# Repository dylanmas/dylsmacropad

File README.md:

# WIP!

Visit the wiki to learn more.

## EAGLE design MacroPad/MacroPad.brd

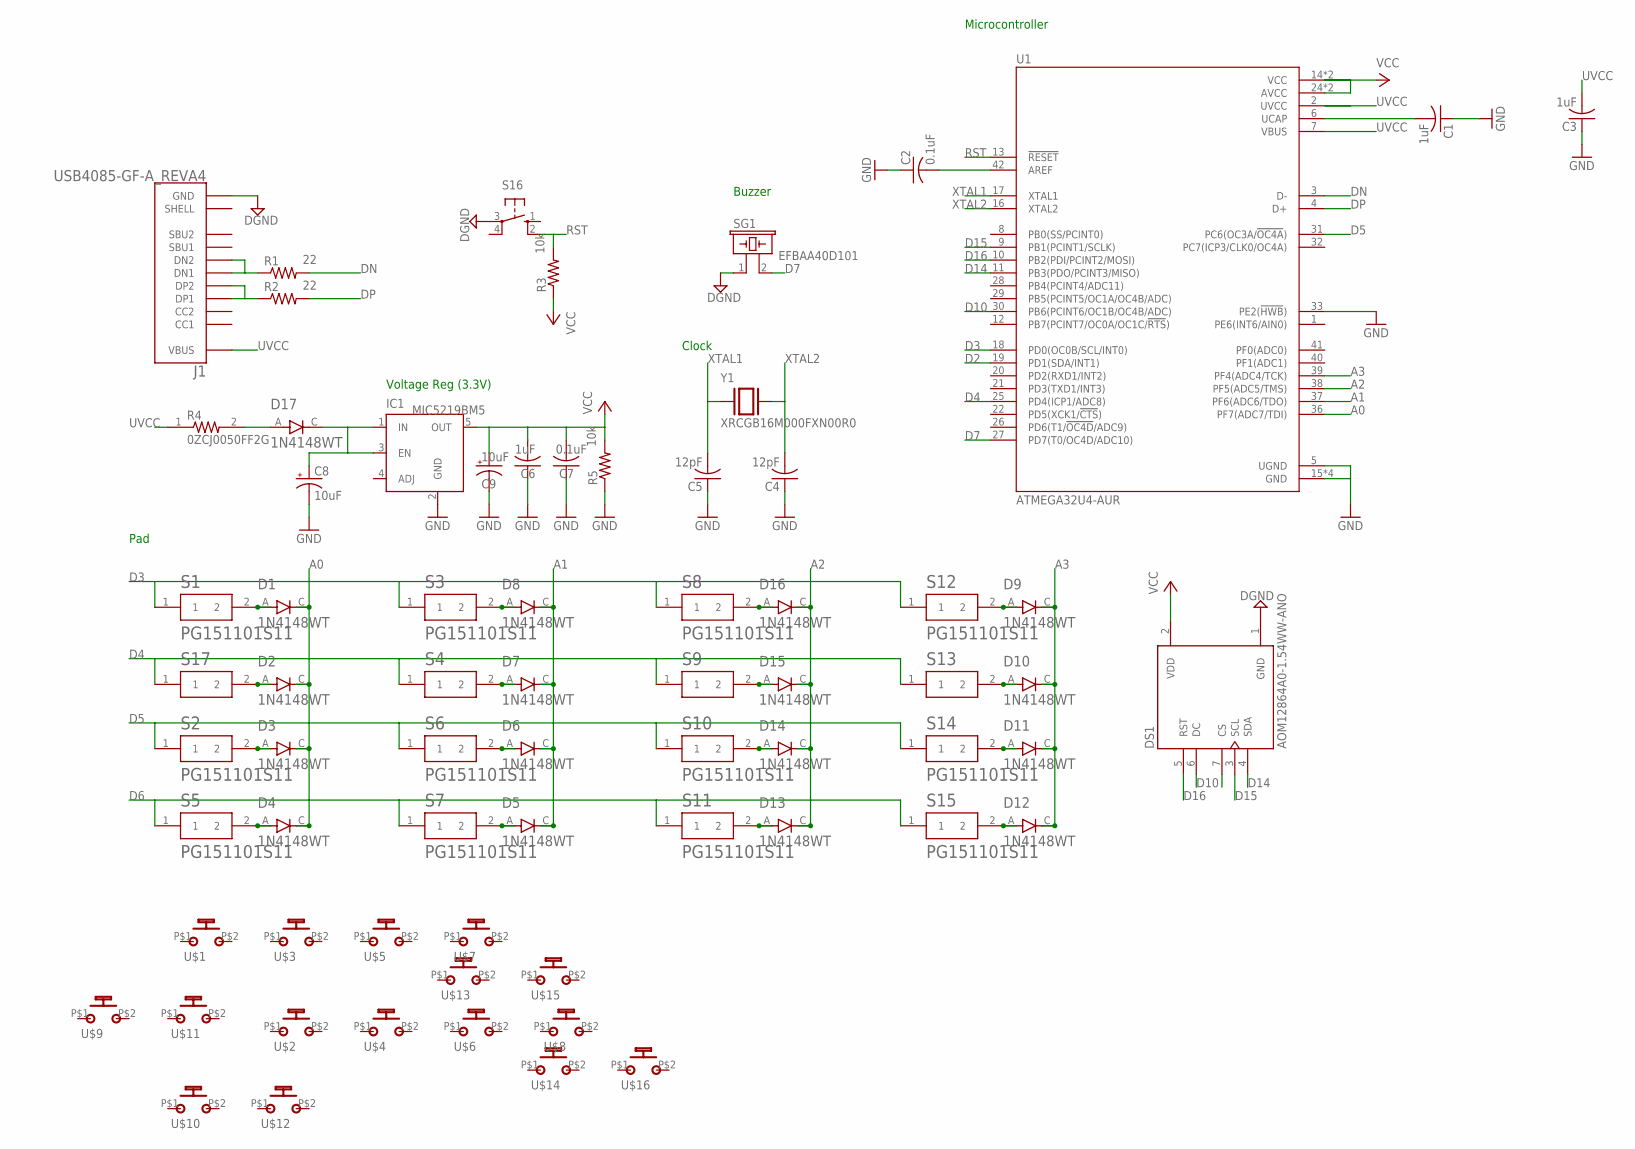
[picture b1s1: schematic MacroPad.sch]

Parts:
C1, C3, C6: 1uF; C0603
C2, C7: 0.1uF; C0603
C4, C5: 12pF; C0603
C8, C9: 10uF; 153CLV-0605
D1, D2, D3, D4, D5, D6, D7, D8, D9, D10, D11, D12, D13, D14, D15, D16, D17: 1N4148WT; SODFL1608X70N
DS1: AOM12864A0-1.54WW-ANO; LCD_AOM12864A0-1.54WW-ANO
IC1: MIC5219BM5; SOT23-5
J1: USB4085-GF-A_REVA4; GCT_USB4085-GF-A_REVA4
R1, R2: 22; R0805
R3, R5: 10k; R0805
R4: 0ZCJ0050FF2G; RESC3216X125N
S1, S2, S3, S4, S5, S6, S7, S8, S9, S10, S11, S12, S13, S14, S15, S17: PG151101S11; SW_PG151101S11
S16: 10-XX; B3F-10XX
SG1: EFBAA40D101
U1: ATMEGA32U4-AUR; QFP80P1200X1200X120-44N
U$1, U$2, U$3, U$4, U$5, U$6, U$7, U$8, U$9, U$10, U$11, U$12, U$13, U$14, U$15, U$16: MX1A-11NN; CHERRY_MX1A-11NN_SWITCH
Y1: XRCGB16M000FXN00R0; OSC_XRCGB16M000FXN00R0

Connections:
A0: D1.C, D2.C, D3.C, D4.C, U1.36 (PF7(ADC7/TDI))
A1: D5.C, D6.C, D7.C, D8.C, U1.37 (PF6(ADC6/TDO))
A2: D13.C, D14.C, D15.C, D16.C, U1.38 (PF5(ADC5/TMS))
A3: D9.C, D10.C, D11.C, D12.C, U1.39 (PF4(ADC4/TCK))
D2: U1.19 (PD1(SDA/INT1))
D3: S1.1, S3.1, S8.1, S12.1, U1.18 (PD0(OC0B/SCL/INT0))
D4: S4.1, S9.1, S13.1, S17.1, U1.25 (PD4(ICP1/ADC8))
D5: S2.1, S6.1, S10.1, S14.1, U1.31 (PC6(OC3A/!OC4A!))
D6: S5.1, S7.1, S11.1, S15.1
D7: SG1.2, U1.27 (PD7(T0/OC4D/ADC10))
D10: DS1.6 (DC), U1.30 (PB6(PCINT6/OC1B/OC4B/ADC))
D14: DS1.4 (SDA), U1.11 (PB3(PDO/PCINT3/MISO))
D15: DS1.3 (SCL), U1.9 (PB1(PCINT1/SCLK))
D16: DS1.5 (RST), U1.10 (PB2(PDI/PCINT2/MOSI))
DGND: DS1.1 (GND), J1.A1 (GND), J1.A12 (GND), J1.B1 (GND), J1.B12 (GND), S16.3, SG1.1
DN: R1.2, U1.3 (D-)
DP: R2.2, U1.4 (D+)
GND: C1.1, C2.1, C3.1, C4.1, C5.1, C6.1, C7.1, C8.-, C9.-, IC1.2 (GND), R5.1, U1.5 (UGND), U1.15 (GND), U1.23 (GND), U1.33 (PE2(!HWB!)), U1.35 (GND), U1.43 (GND)
unnamed: D1.A, S1.2
unnamed: D2.A, S17.2
unnamed: D3.A, S2.2
unnamed: D4.A, S5.2
unnamed: D8.A, S3.2
unnamed: D7.A, S4.2
unnamed: D6.A, S6.2
unnamed: D5.A, S7.2
unnamed: D16.A, S8.2
unnamed: D15.A, S9.2
unnamed: D14.A, S10.2
unnamed: D13.A, S11.2
unnamed: D9.A, S12.2
unnamed: D10.A, S13.2
unnamed: D11.A, S14.2
unnamed: D12.A, S15.2
unnamed: D17.A, R4.2
unnamed: J1.A7 (DN1), J1.B7 (DN2), R1.1
unnamed: J1.A6 (DP1), J1.B6 (DP2), R2.1
unnamed: C1.2, U1.6 (UCAP)
unnamed: C2.2, U1.42 (AREF)
unnamed: C8.+, D17.C, IC1.1 (IN), IC1.3 (EN)
RST: R3.2, S16.2 (S1), U1.13 (!RESET)
UVCC: C3.2, J1.A4 (VBUS), J1.A9 (VBUS), J1.B4 (VBUS), J1.B9 (VBUS), R4.1, U1.2 (UVCC), U1.7 (VBUS)
VCC: C6.2, C7.2, C9.+, DS1.2 (VDD), IC1.5 (OUT), R3.1, R5.2, U1.14 (VCC), U1.24 (AVCC), U1.34 (VCC), U1.44 (AVCC)
XTAL1: C5.2, U1.17 (XTAL1), Y1.1
XTAL2: C4.2, U1.16 (XTAL2), Y1.3

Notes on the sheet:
Pad
Buzzer
Microcontroller
Clock
Voltage Reg (3.3V)

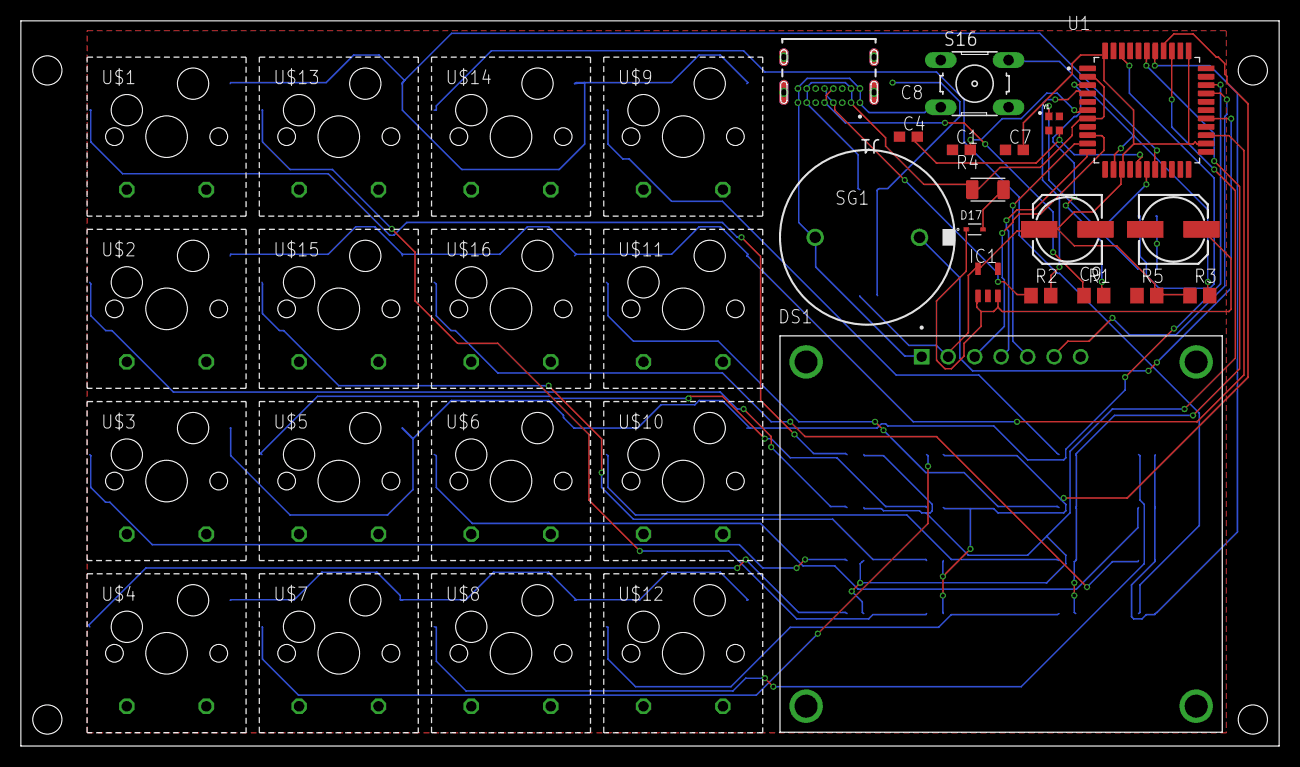
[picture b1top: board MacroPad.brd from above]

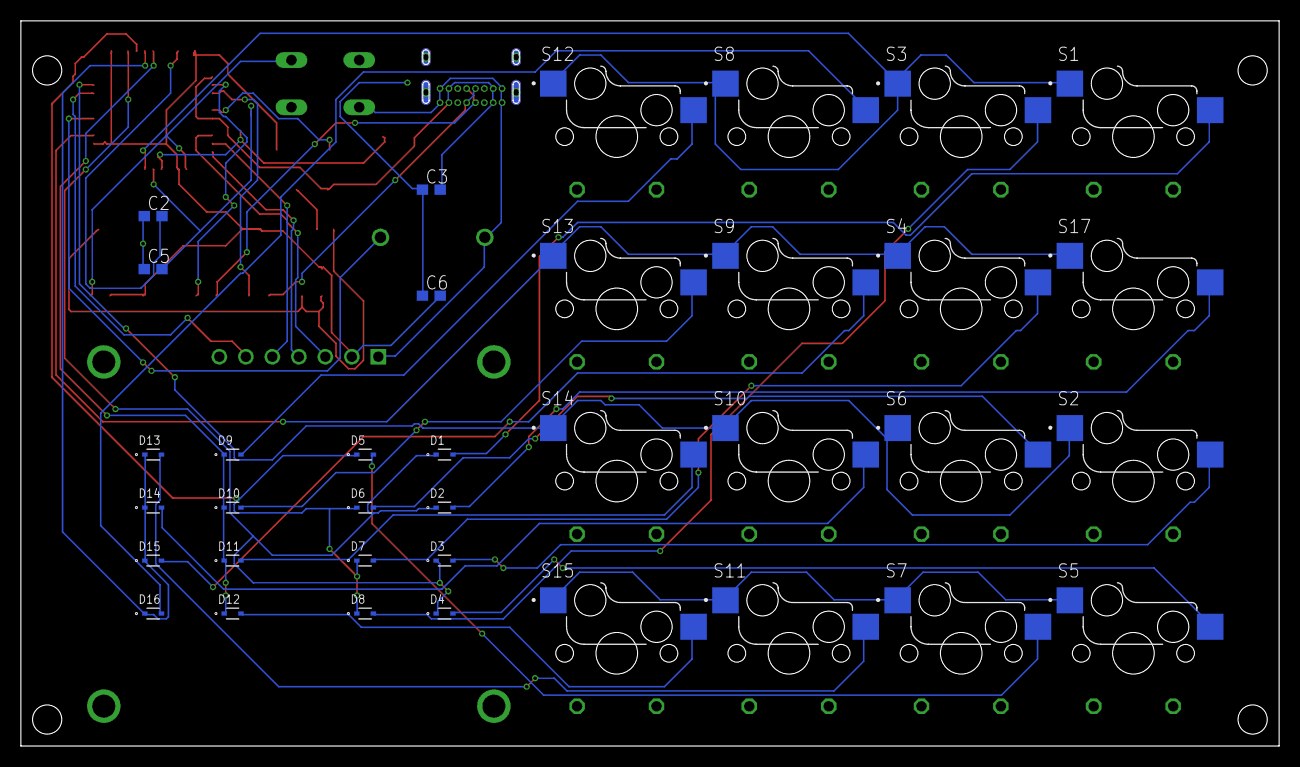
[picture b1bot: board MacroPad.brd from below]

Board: 2 copper layers, 120.6 x 69.5 mm, 70 parts (36 on the bottom side), 44 nets.

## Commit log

2022-11-27 Added schematic + board files
2022-11-27 Initial program added
2022-11-27 Fixed some DRC errors
2022-11-27 Problematic DRC issues cleared
2022-11-27 Added missing diode
2022-11-28 Further board errors corrected, BOM included
2022-11-28 CAM Output updated
2022-11-29 Reorganizing of project structure
2022-11-29 Added placeholders to maintain project structure
2022-11-29 Initial placeholder
2022-11-30 Adding SvelteKit to pages
2022-11-30 Test commit
2022-11-30 Test commit 2
2022-11-30 Added tailwind
2022-11-30 Added software scaffolding
2022-12-03 Software home screen + COM port reading done
2022-12-03 Added delay to fix inaccurate inputs
2022-12-04 Added CS pin for display to schematic + board
    The CS pin was initially left not connected intentionally, because I was led to believe that the CS pin was only needed when using multiple devices on SPI. However, for displays like the one used, th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
2022-12-07 Added screen functionality, software config screen
2022-12-07 Included Arduino binary and file in bundle
2022-12-07 Changed program formatting
2022-12-16 More progress on software
